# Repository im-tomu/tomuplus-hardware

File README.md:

# THIS PROJECT HAS BEEN ABANDONED!

The Tomu+ has been abandoned and is not under development.

<br>
<br>
<br>
<br>
<br>
<br>
<br>
<br>
<br>
<br>
<br>
<br>
<br>
<br>
<br>
<br>
<br>
<br>
<br>
<br>
<br>
<br>
<br>
<br>
<br>
<br>
<br>
<br>
<br>
<br>
<br>
<br>
<br>
<br>
<br>
<br>
<br>
<br>
<br>

----

# [Tomu+, I'm](tomu.im)

[I'm Tomu+](tomu.im) a *improved* tiny ARM microprocessor which fits in your USB port.
I have two buttons and two LEDs.

## Contact

 * [Announcement mailing list](https://groups.google.com/forum/#!forum/tomu-announce/join) - Low traffic list for announcements.
 * [Discussion mailing list](https://groups.google.com/forum/#!forum/tomu-discuss/join) - List for discussing development / new features / etc.
 * [IRC Channel - irc://irc.freenode.net/#tomu](https://webchat.freenode.net/?channels=#tomu) - IRC channel for discussing anything related to the project.

## WARNING: This design hasn't been proven yet!

Built out of a 3d printed part + 2 layer "thin" PCB (0.4mm or 0.6mm thick).

The board has;
 * 6mil traces
 * 6mil clearance
 * 0.3mm drill / 0.6mm vias

--

Uses a Freescale Semiconductor / NXP Kinetis KL27 (MKL27Z256VFM4) ([datasheet](http://cache.freescale.com/files/32bit/doc/data_sheet/KL27P64M48SF6.pdf)).

The important features are;
 * [~$5.00 USD on Digikey](https://www.digikey.com.au/product-detail/en/freescale-semiconductor-nxp/MKL27Z256VFM4/MKL27Z256VFM4-ND/4988919)
 * QFN32 - 5mm x 5mm package
 * Inbuilt 5V to 3V3 regulator.
 * Crystal-less USB

These make something which is almost hand solder-able fit into the tiny size.

## BOM

All parts are ordered from Digikey but could easily be ordered from somewhere else.

 * [Digikey BOM in CSV format](bom-digikey.csv)

Individual parts;

 * Resistors
  - 2 x 0402 - 33 Ohm - [Digikey](https://www.digikey.com.au/short/35385r)
  - 2 x 0402 - ~50 Ohm (Depends on LED choice)
  - 1 x 0402 - 10k Ohm

 * Capacitors - [Digikey Capacitors 0402, >1uF](https://www.digikey.com.au/short/3m8r4z)
  - 1 x Capacitor ~2.2uF 0402
  - 1 x Capacitor ~4.7uF 0402

 * 2 x LED 0402
  - You choice of two different colors (might require adjustment of R1/R2).
  - 5mA LEDs are better choice.
  - Get highest millicandela rating you can.
  - [Digikey Search of LEDs in 0402 package](https://www.digikey.com.au/short/3m8rz0)

 * 1 x MKL27Z256VFM4 - [Digikey](https://www.digikey.com.au/short/353852)

 * (Optional) 1 x Atmel ATECC508A Auth IC - [Digikey](https://www.digikey.com.au/short/35385n)

## TODO

 * Create the device
 * Create the 3d print model.
 * Write the firmware for the device.

## FAQ

##### Why did you create this?

The aim was to prove that a device which fits in your USB port could be created
**by hobbists in small quantities** extremely cheaply.

##### Where does the name Tomu come from?

TOMU comes from the abbreviation "Tim's Open Micro USB".

##### What can I use this for?

What ever you want! If you do create something, please send me the info!

## License

The contents of this repository excluding "third_party" folder is released
under your choice of the following two licences:

 * the "Creative Commons Attribution-ShareAlike 4.0 International License"
   (CC BY-SA 4.0) full text of this license is included in the LICENSE file
   and a copy can also be found at
   http://creativecommons.org/licenses/by-sa/4.0/

 * the "TAPR Open Hardware License" full text of this license is included
   in the LICENSE file and a copy can also be found at
   http://www.tapr.org/OHL

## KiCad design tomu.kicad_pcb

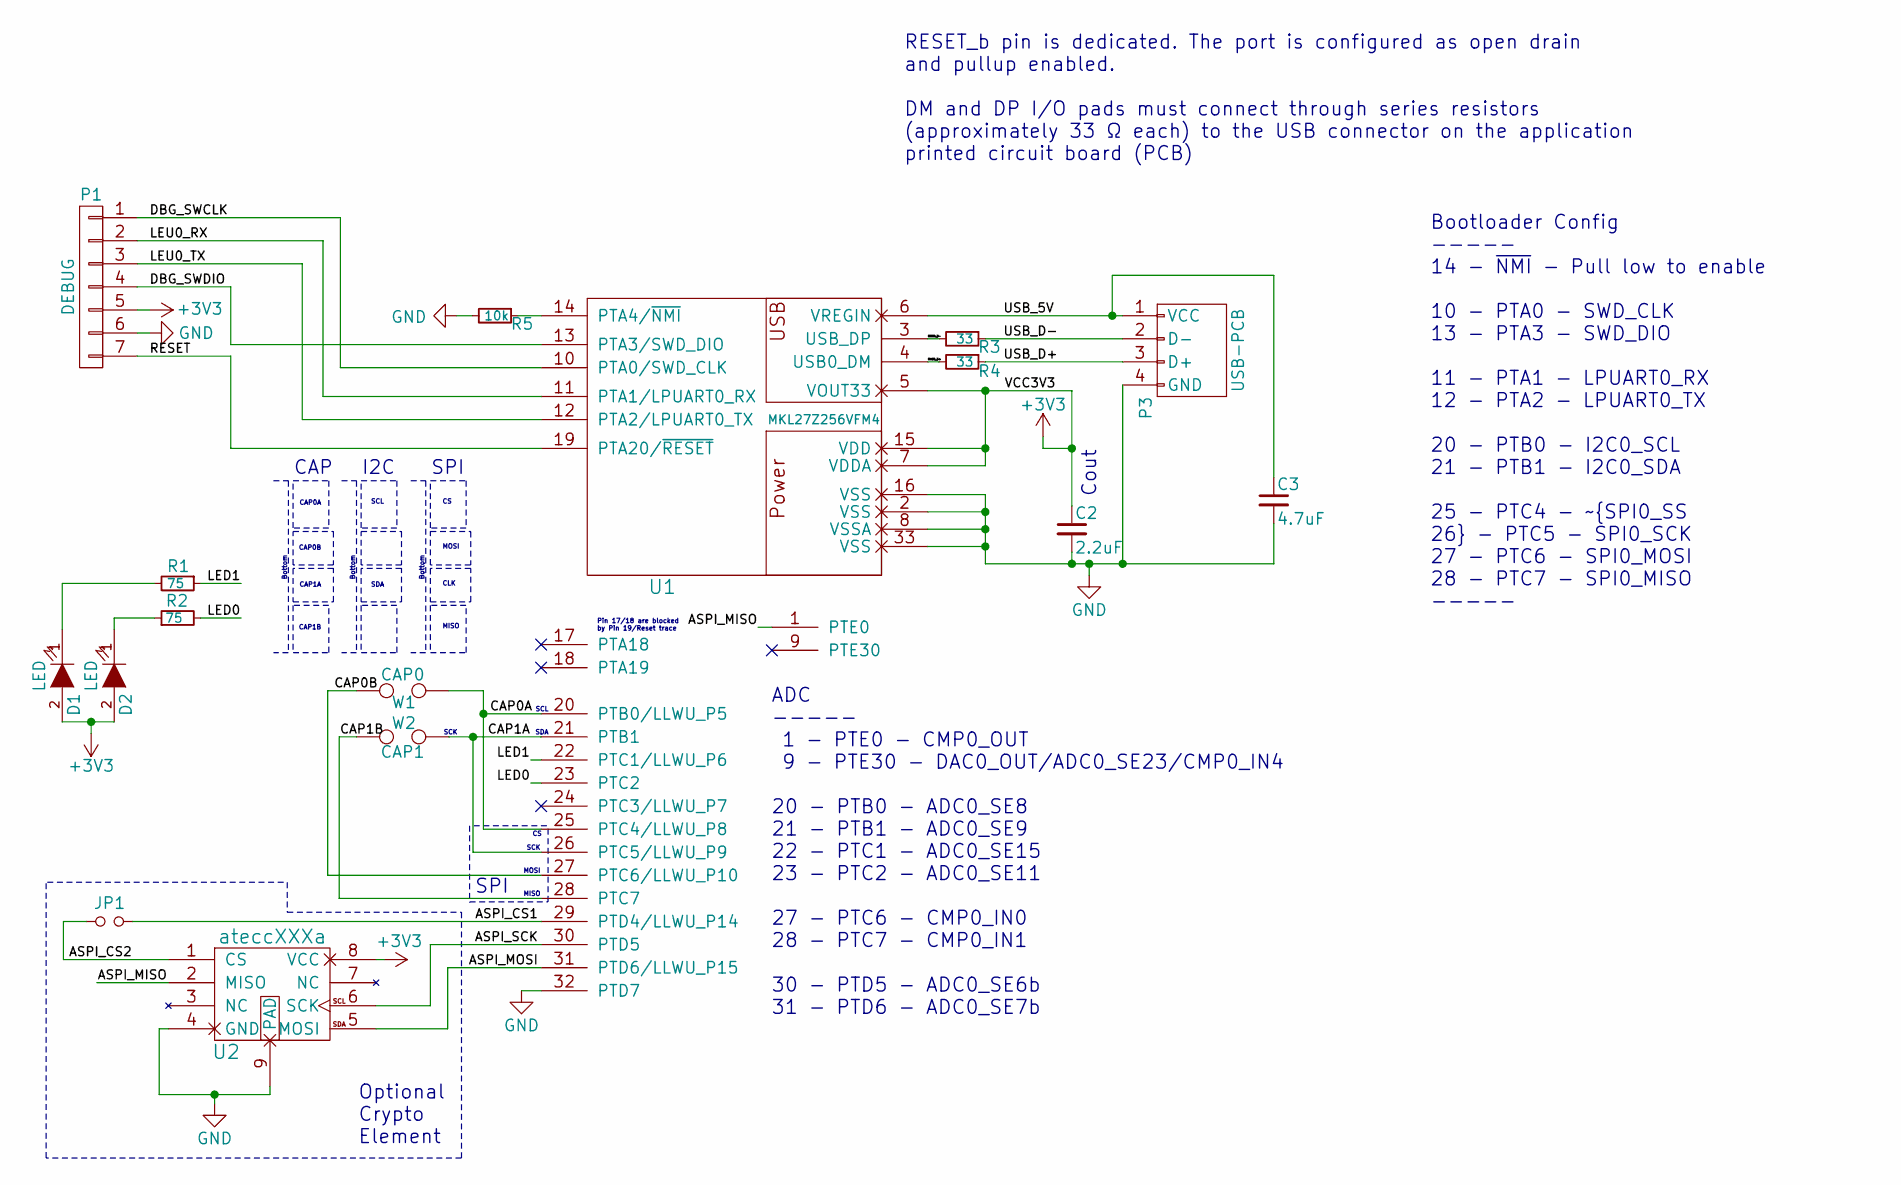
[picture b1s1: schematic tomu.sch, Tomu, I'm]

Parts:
C2: 2.2uF; C_0402
C3: 4.7uF; C_0402
D1, D2: LED; LED_0402
JP1: Jumper_NO_Small; R_0402
P1: DEBUG; debug-points-127mm
P3: USB-PCB
R1, R2: 75; R_0402
R3, R4: 33; R_0402
R5: 10k; R_0402
U1: MKL27Z256VFM4; QFN-32-1EP_5x5mm_Pitch0.5mm
U2: ateccXXXa; DFN-8-1EP_3x2mm_Pitch0.5mm
W1: CAP0; cap-points
W2: CAP1; cap-points

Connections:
+3V3: C2.1, D1.2 (A), D2.2 (A), P1.5, U1.5 (VOUT33), U1.7 (VDDA), U1.15 (VDD), U2.8 (VCC)
/ASPI_CS1: JP1.2, U1.29 (PTD4/LLWU_P14)
/ASPI_CS2: JP1.1, U2.1 (CS)
/ASPI_MISO: U1.1 (PTE0), U2.2 (MISO)
/ASPI_MOSI: U1.31 (PTD6/LLWU_P15), U2.5 (MOSI)
/ASPI_SCK: U1.30 (PTD5), U2.6 (SCK)
/CAP0A: U1.20 (PTB0/LLWU_P5), U1.25 (PTC4/LLWU_P8), W1.1
/CAP0B: U1.27 (PTC6/LLWU_P10), W1.2
/CAP1A: U1.21 (PTB1), U1.26 (PTC5/LLWU_P9), W2.1
/CAP1B: U1.28 (PTC7), W2.2
/DBG_SWCLK: P1.1, U1.10 (PTA0/SWD_CLK)
/DBG_SWDIO: P1.4, U1.13 (PTA3/SWD_DIO)
/LED0: R2.2, U1.23 (PTC2)
/LED1: R1.1, U1.22 (PTC1/LLWU_P6)
/LEU0_RX: P1.2, U1.11 (PTA1/LPUART0_RX)
/LEU0_TX: P1.3, U1.12 (PTA2/LPUART0_TX)
/RESET: P1.7, U1.19 (PTA20/~RESET)
/RUSB_D+: R4.2, U1.4 (USB0_DM)
/RUSB_D-: R3.2, U1.3 (USB_DP)
/USB_5V: C3.1, P3.1 (VCC), U1.6 (VREGIN)
/USB_D+: P3.3 (D+), R4.1
/USB_D-: P3.2 (D-), R3.1
GND: C2.2, C3.2, P1.6, P3.4 (GND), R5.2, U1.2 (VSS), U1.8 (VSSA), U1.16 (VSS), U1.32 (PTD7), U1.33 (VSS), U2.4 (GND), U2.9 (PAD)
unnamed: D1.1 (K), R1.2
unnamed: D2.1 (K), R2.1
unnamed: R5.1, U1.14 (PTA4/~NMI)

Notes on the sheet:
Bootloader Config ----- 14 - ~NMI~ - Pull low to enable 10 - PTA0 - SWD_CLK 13 - PTA3 - SWD_DIO 11 - PTA1 - LPUART0_RX 12 - PTA2 - LPUART0_TX 20 - PTB0 - I2C0_SCL 21 - PTB1 - I2C0_SDA 25 - PTC4 - ~SPI0_SS 26 - PTC5 - SPI0_SCK 27 - PTC6 - SPI0_MOSI 28 - PTC7 - SPI0_MISO -----
Cout
RESET_b pin is dedicated. The port is configured as open drain and pullup enabled. DM and DP I/O pads must connect through series resistors (approximately 33 Ω each) to the USB connector on the application printed circuit board (PCB)
Pin 17/18 are blocked by Pin 19/Reset trace
ADC ----- 1 - PTE0 - CMP0_OUT 9 - PTE30 - DAC0_OUT/ADC0_SE23/CMP0_IN4 20 - PTB0 - ADC0_SE8 21 - PTB1 - ADC0_SE9 22 - PTC1 - ADC0_SE15 23 - PTC2 - ADC0_SE11 27 - PTC6 - CMP0_IN0 28 - PTC7 - CMP0_IN1 30 - PTD5 - ADC0_SE6b 31 - PTD6 - ADC0_SE7b
SPI
SCK
MOSI
MISO
SCL
SDA
CAP0A
CAP0B
CAP1A
CAP1B
CLK
I2C
CAP
Bottom
Optional Crypto Element

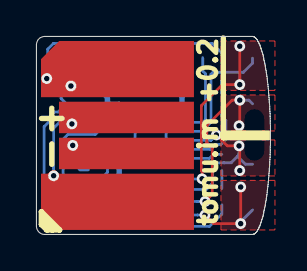
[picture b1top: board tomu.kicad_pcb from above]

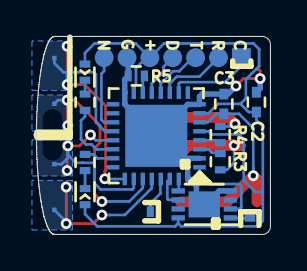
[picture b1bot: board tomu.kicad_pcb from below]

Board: 2 copper layers, 13.0 x 11.0 mm, 16 parts (15 on the bottom side), 26 nets.

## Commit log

2016-09-09 Starting to do a version based on Kinetis KL27 microcontroller.
2016-09-09 Updating the README.
2016-09-09 Changing.
2016-09-09 Starting to make the component.
2016-09-10 Adding contact info.
2016-09-10 Slowly making work...
2016-09-10 Lots of small updates.
2016-09-12 Getting closer to working.
2016-11-25 Working on the debug header.
2016-11-25 More work...
2016-11-25 Adding atecc508a part.
2016-11-26 Allow any of the ATECC parts.
2016-11-26 Temp commit before net import.
2016-11-26 Another temp commit.
2016-11-26 More improvements.
2016-11-26 Fully routed design which passes DRC.
2016-11-26 Making the gnd traces thicker.
2016-11-26 Improving the silkscreen.
2016-11-26 Updating the release script for + version.
2016-11-26 Update the README a little.
2016-11-26 Removing the base Tomu releases from directory.
2016-11-26 Only match Tomu+ release tags.
2016-11-26 Setting version to +0.0
2016-11-26 Change export settings slightly.
2016-11-26 Changing the output settings slightly.
2016-11-26 Fixing release script.
2016-11-26 Adding slot.
2016-11-26 Fixing a GND trace.
2016-11-26 Adjust a trace.
2016-11-26 Bumping version to +0.1
2016-11-26 Pull the atmel chip in further.
2016-11-26 Bumping version to +0.2
2016-11-26 Updating the images.
2016-11-26 Updating the BOM a little.
2016-12-29 Add compatibility with archlinux for releases
    As defined in PEP 394 the version of python should be
    specified when executing a script, due to archlinux
    and similar distributions pointing python to python3
    rather than python2. gen_gerber_and_drill_files_board.py
    is written in python 2 therefore won't work on archlinux
    and similar distributions.
2016-12-29 Closed small gap in Edge.Cuts layer
    Small gap prevented 3D viewer from properly rendering outline
2017-12-28 Marking the project as abandoned.
    # THIS PROJECT HAS BEEN ABANDONED!
    The Tomu+ has been abandoned and is not under development.

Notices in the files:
tomu.kicad_pcb:
License: CC-BY-SA 4.0 or TAPR
